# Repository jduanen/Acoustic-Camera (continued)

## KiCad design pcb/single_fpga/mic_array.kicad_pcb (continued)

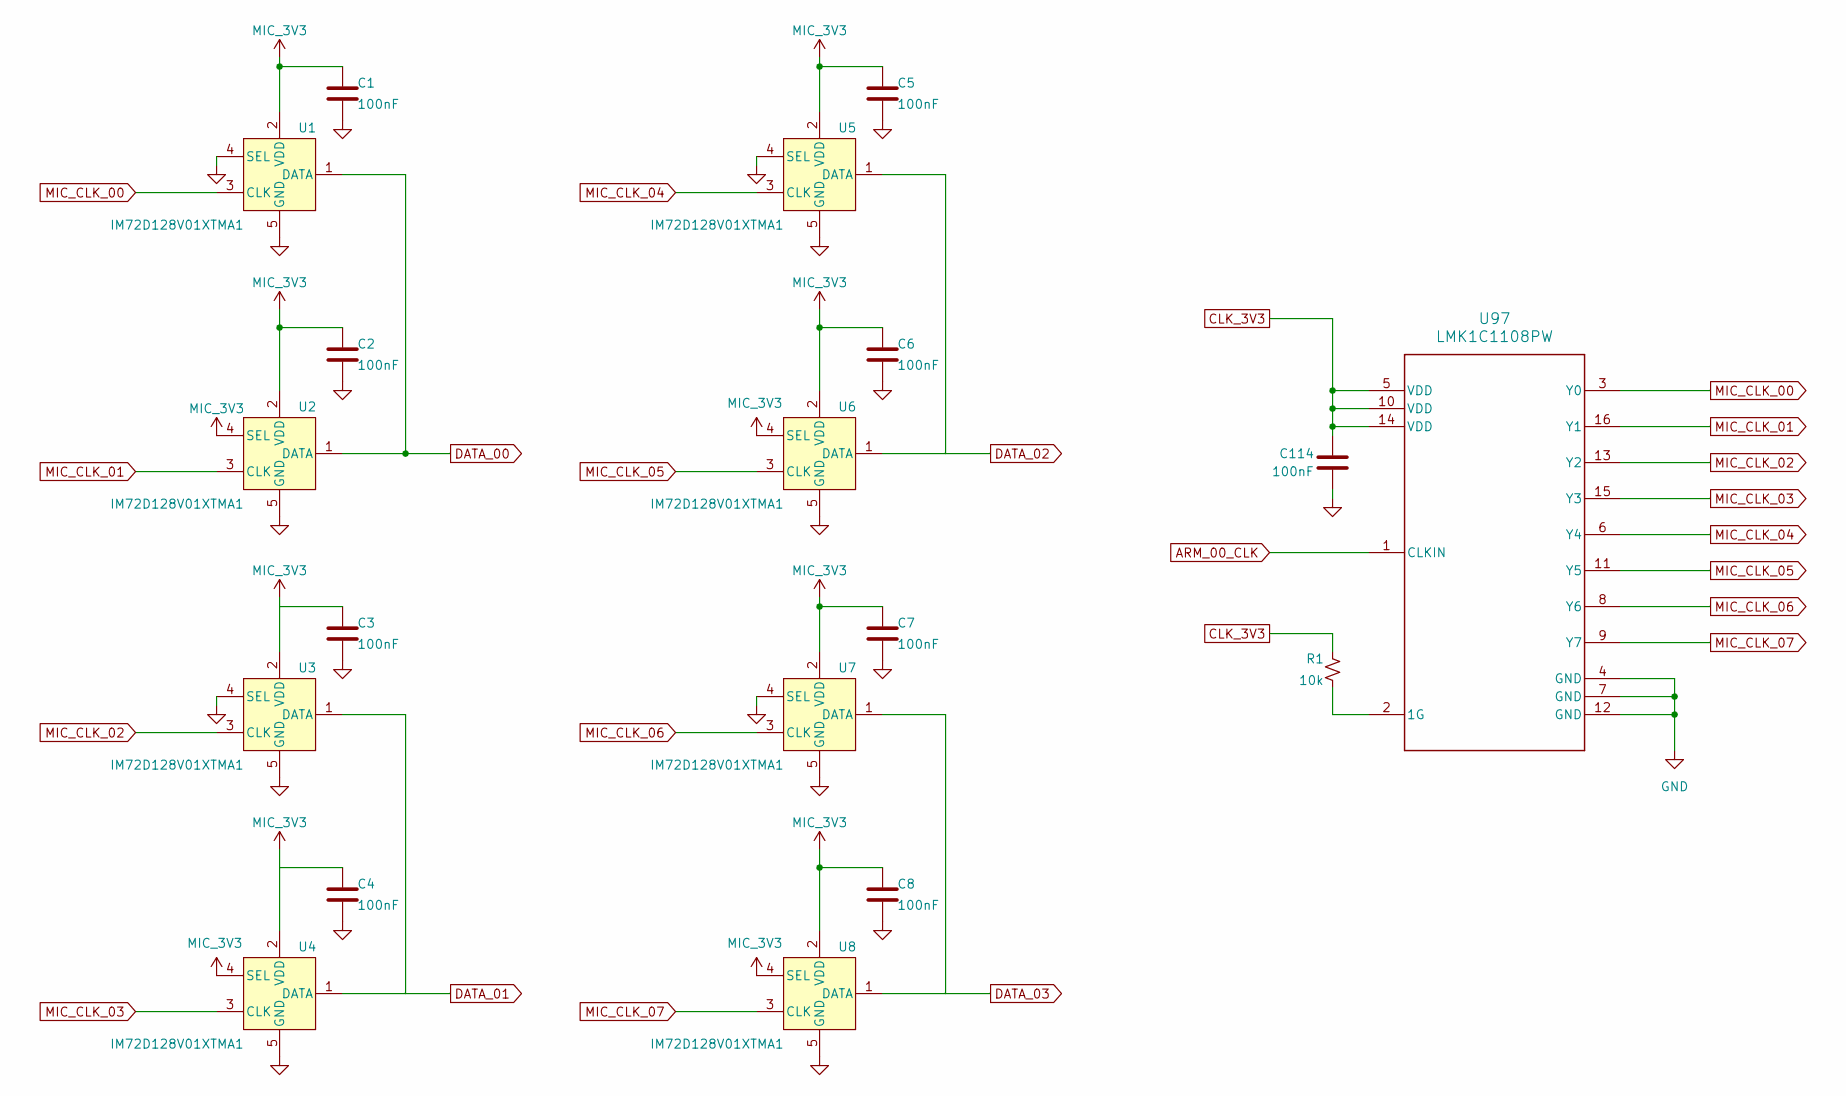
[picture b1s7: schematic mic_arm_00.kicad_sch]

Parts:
C1, C2, C3, C4, C5, C6, C7, C8, C114: 100nF; C_0603_1608Metric; Part Number CC0603KRX7R9BB104; LCSC Part # C14663
R1: 10k; R_0603_1608Metric; Part Number 0603WAF1002T5E; LCSC Part # C25804
U1, U2, U3, U4, U5, U6, U7, U8: IM72D128V01XTMA1; IFX-PG-LLGA-5-4; Part Number IM72D128V01XTMA1; LCSC Part # C5119248
U97: LMK1C1108PW; PW0016A_N; Part Number LMK1C1108PWR; LCSC Part # C2868241

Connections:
ARM_00_CLK: U97.1 (CLKIN); also elsewhere on the board
CLK_3V3: C114.2, R1.2, U97.5 (VDD), U97.10 (VDD), U97.14 (VDD); also elsewhere on the board
DATA_00: U1.1 (DATA), U2.1 (DATA); also elsewhere on the board
DATA_01: U3.1 (DATA), U4.1 (DATA); also elsewhere on the board
DATA_02: U5.1 (DATA), U6.1 (DATA); also elsewhere on the board
DATA_03: U7.1 (DATA), U8.1 (DATA); also elsewhere on the board
GND: C1.2, C2.2, C3.2, C4.2, C5.2, C6.2, C7.2, C8.2, C114.1, U1.4 (SEL), U1.5 (GND), U2.5 (GND), U3.4 (SEL), U3.5 (GND), U4.5 (GND), U5.4 (SEL), U5.5 (GND), U6.5 (GND), U7.4 (SEL), U7.5 (GND), U8.5 (GND), U97.4 (GND), U97.7 (GND), U97.12 (GND); also elsewhere on the board
MIC_3V3: C1.1, C2.1, C3.1, C4.1, C5.1, C6.1, C7.1, C8.1, U1.2 (VDD), U2.2 (VDD), U2.4 (SEL), U3.2 (VDD), U4.2 (VDD), U4.4 (SEL), U5.2 (VDD), U6.2 (VDD), U6.4 (SEL), U7.2 (VDD), U8.2 (VDD), U8.4 (SEL); also elsewhere on the board
MIC_CLK_00: U1.3 (CLK), U97.3 (Y0)
MIC_CLK_01: U2.3 (CLK), U97.16 (Y1)
MIC_CLK_02: U3.3 (CLK), U97.13 (Y2)
MIC_CLK_03: U4.3 (CLK), U97.15 (Y3)
MIC_CLK_04: U5.3 (CLK), U97.6 (Y4)
MIC_CLK_05: U6.3 (CLK), U97.11 (Y5)
MIC_CLK_06: U7.3 (CLK), U97.8 (Y6)
MIC_CLK_07: U8.3 (CLK), U97.9 (Y7)
unnamed: R1.1, U97.2 (1G)

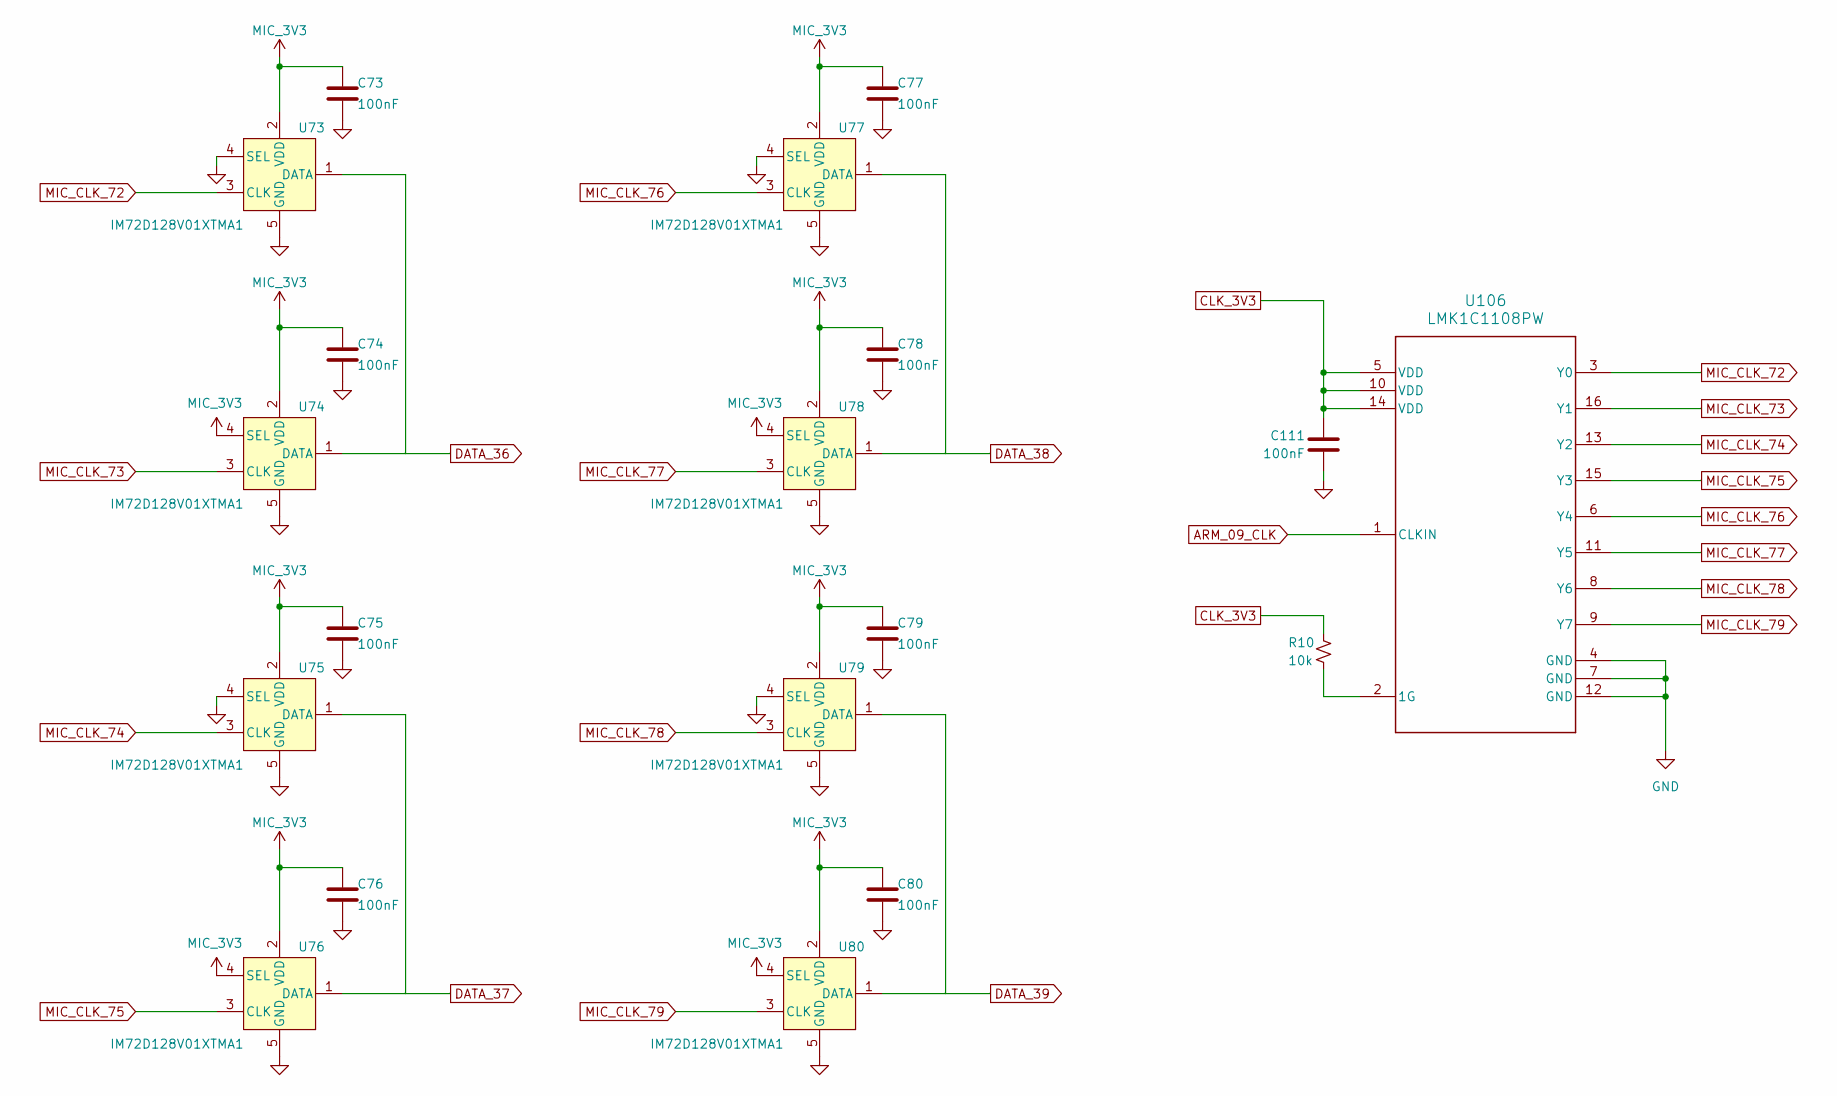
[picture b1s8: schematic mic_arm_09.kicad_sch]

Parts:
C73, C74, C75, C76, C77, C78, C79, C80, C111: 100nF; C_0603_1608Metric; Part Number CC0603KRX7R9BB104; LCSC Part # C14663
R10: 10k; R_0603_1608Metric; Part Number 0603WAF1002T5E; LCSC Part # C25804
U73, U74, U75, U76, U77, U78, U79, U80: IM72D128V01XTMA1; IFX-PG-LLGA-5-4; Part Number IM72D128V01XTMA1; LCSC Part # C5119248
U106: LMK1C1108PW; PW0016A_N; Part Number LMK1C1108PWR; LCSC Part # C2868241

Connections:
ARM_09_CLK: U106.1 (CLKIN); also elsewhere on the board
CLK_3V3: C111.2, R10.2, U106.5 (VDD), U106.10 (VDD), U106.14 (VDD); also elsewhere on the board
DATA_36: U73.1 (DATA), U74.1 (DATA); also elsewhere on the board
DATA_37: U75.1 (DATA), U76.1 (DATA); also elsewhere on the board
DATA_38: U77.1 (DATA), U78.1 (DATA); also elsewhere on the board
DATA_39: U79.1 (DATA), U80.1 (DATA); also elsewhere on the board
GND: C73.2, C74.2, C75.2, C76.2, C77.2, C78.2, C79.2, C80.2, C111.1, U73.4 (SEL), U73.5 (GND), U74.5 (GND), U75.4 (SEL), U75.5 (GND), U76.5 (GND), U77.4 (SEL), U77.5 (GND), U78.5 (GND), U79.4 (SEL), U79.5 (GND), U80.5 (GND), U106.4 (GND), U106.7 (GND), U106.12 (GND); also elsewhere on the board
MIC_3V3: C73.1, C74.1, C75.1, C76.1, C77.1, C78.1, C79.1, C80.1, U73.2 (VDD), U74.2 (VDD), U74.4 (SEL), U75.2 (VDD), U76.2 (VDD), U76.4 (SEL), U77.2 (VDD), U78.2 (VDD), U78.4 (SEL), U79.2 (VDD), U80.2 (VDD), U80.4 (SEL); also elsewhere on the board
MIC_CLK_72: U73.3 (CLK), U106.3 (Y0)
MIC_CLK_73: U74.3 (CLK), U106.16 (Y1)
MIC_CLK_74: U75.3 (CLK), U106.13 (Y2)
MIC_CLK_75: U76.3 (CLK), U106.15 (Y3)
MIC_CLK_76: U77.3 (CLK), U106.6 (Y4)
MIC_CLK_77: U78.3 (CLK), U106.11 (Y5)
MIC_CLK_78: U79.3 (CLK), U106.8 (Y6)
MIC_CLK_79: U80.3 (CLK), U106.9 (Y7)
unnamed: R10.1, U106.2 (1G)

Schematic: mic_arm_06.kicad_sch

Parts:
C49, C50, C51, C52, C53, C54, C55, C56, C108: 100nF; C_0603_1608Metric; Part Number CC0603KRX7R9BB104; LCSC Part # C14663
R7: 10k; R_0603_1608Metric; Part Number 0603WAF1002T5E; LCSC Part # C25804
U49, U50, U51, U52, U53, U54, U55, U56: IM72D128V01XTMA1; IFX-PG-LLGA-5-4; Part Number IM72D128V01XTMA1; LCSC Part # C5119248
U103: LMK1C1108PW; PW0016A_N; Part Number LMK1C1108PWR; LCSC Part # C2868241

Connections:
ARM_06_CLK: U103.1 (CLKIN); also elsewhere on the board
CLK_3V3: C108.2, R7.2, U103.5 (VDD), U103.10 (VDD), U103.14 (VDD); also elsewhere on the board
DATA_24: U49.1 (DATA), U50.1 (DATA); also elsewhere on the board
DATA_25: U51.1 (DATA), U52.1 (DATA); also elsewhere on the board
DATA_26: U53.1 (DATA), U54.1 (DATA); also elsewhere on the board
DATA_27: U55.1 (DATA), U56.1 (DATA); also elsewhere on the board
GND: C49.2, C50.2, C51.2, C52.2, C53.2, C54.2, C55.2, C56.2, C108.1, U49.4 (SEL), U49.5 (GND), U50.5 (GND), U51.4 (SEL), U51.5 (GND), U52.5 (GND), U53.4 (SEL), U53.5 (GND), U54.5 (GND), U55.4 (SEL), U55.5 (GND), U56.5 (GND), U103.4 (GND), U103.7 (GND), U103.12 (GND); also elsewhere on the board
MIC_3V3: C49.1, C50.1, C51.1, C52.1, C53.1, C54.1, C55.1, C56.1, U49.2 (VDD), U50.2 (VDD), U50.4 (SEL), U51.2 (VDD), U52.2 (VDD), U52.4 (SEL), U53.2 (VDD), U54.2 (VDD), U54.4 (SEL), U55.2 (VDD), U56.2 (VDD), U56.4 (SEL); also elsewhere on the board
MIC_CLK_48: U49.3 (CLK), U103.3 (Y0)
MIC_CLK_49: U50.3 (CLK), U103.16 (Y1)
MIC_CLK_50: U51.3 (CLK), U103.13 (Y2)
MIC_CLK_51: U52.3 (CLK), U103.15 (Y3)
MIC_CLK_52: U53.3 (CLK), U103.6 (Y4)
MIC_CLK_53: U54.3 (CLK), U103.11 (Y5)
MIC_CLK_54: U55.3 (CLK), U103.8 (Y6)
MIC_CLK_55: U56.3 (CLK), U103.9 (Y7)
unnamed: R7.1, U103.2 (1G)

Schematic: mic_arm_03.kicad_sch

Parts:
C25, C26, C27, C28, C29, C30, C31, C32, C105: 100nF; C_0603_1608Metric; Part Number CC0603KRX7R9BB104; LCSC Part # C14663
R4: 10k; R_0603_1608Metric; Part Number 0603WAF1002T5E; LCSC Part # C25804
U25, U26, U27, U28, U29, U30, U31, U32: IM72D128V01XTMA1; IFX-PG-LLGA-5-4; Part Number IM72D128V01XTMA1; LCSC Part # C5119248
U100: LMK1C1108PW; PW0016A_N; Part Number LMK1C1108PWR; LCSC Part # C2868241

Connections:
ARM_03_CLK: U100.1 (CLKIN); also elsewhere on the board
CLK_3V3: C105.2, R4.2, U100.5 (VDD), U100.10 (VDD), U100.14 (VDD); also elsewhere on the board
DATA_12: U25.1 (DATA), U26.1 (DATA); also elsewhere on the board
DATA_13: U27.1 (DATA), U28.1 (DATA); also elsewhere on the board
DATA_14: U29.1 (DATA), U30.1 (DATA); also elsewhere on the board
DATA_15: U31.1 (DATA), U32.1 (DATA); also elsewhere on the board
GND: C25.2, C26.2, C27.2, C28.2, C29.2, C30.2, C31.2, C32.2, C105.1, U25.4 (SEL), U25.5 (GND), U26.5 (GND), U27.4 (SEL), U27.5 (GND), U28.5 (GND), U29.4 (SEL), U29.5 (GND), U30.5 (GND), U31.4 (SEL), U31.5 (GND), U32.5 (GND), U100.4 (GND), U100.7 (GND), U100.12 (GND); also elsewhere on the board
MIC_3V3: C25.1, C26.1, C27.1, C28.1, C29.1, C30.1, C31.1, C32.1, U25.2 (VDD), U26.2 (VDD), U26.4 (SEL), U27.2 (VDD), U28.2 (VDD), U28.4 (SEL), U29.2 (VDD), U30.2 (VDD), U30.4 (SEL), U31.2 (VDD), U32.2 (VDD), U32.4 (SEL); also elsewhere on the board
MIC_CLK_24: U25.3 (CLK), U100.3 (Y0)
MIC_CLK_25: U26.3 (CLK), U100.16 (Y1)
MIC_CLK_26: U27.3 (CLK), U100.13 (Y2)
MIC_CLK_27: U28.3 (CLK), U100.15 (Y3)
MIC_CLK_28: U29.3 (CLK), U100.6 (Y4)
MIC_CLK_29: U30.3 (CLK), U100.11 (Y5)
MIC_CLK_30: U31.3 (CLK), U100.8 (Y6)
MIC_CLK_31: U32.3 (CLK), U100.9 (Y7)
unnamed: R4.1, U100.2 (1G)

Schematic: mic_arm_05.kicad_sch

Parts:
C41, C42, C43, C44, C45, C46, C47, C48, C107: 100nF; C_0603_1608Metric; Part Number CC0603KRX7R9BB104; LCSC Part # C14663
R6: 10k; R_0603_1608Metric; Part Number 0603WAF1002T5E; LCSC Part # C25804
U41, U42, U43, U44, U45, U46, U47, U48: IM72D128V01XTMA1; IFX-PG-LLGA-5-4; Part Number IM72D128V01XTMA1; LCSC Part # C5119248
U102: LMK1C1108PW; PW0016A_N; Part Number LMK1C1108PWR; LCSC Part # C2868241

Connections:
ARM_05_CLK: U102.1 (CLKIN); also elsewhere on the board
CLK_3V3: C107.2, R6.2, U102.5 (VDD), U102.10 (VDD), U102.14 (VDD); also elsewhere on the board
DATA_20: U41.1 (DATA), U42.1 (DATA); also elsewhere on the board
DATA_21: U43.1 (DATA), U44.1 (DATA); also elsewhere on the board
DATA_22: U45.1 (DATA), U46.1 (DATA); also elsewhere on the board
DATA_23: U47.1 (DATA), U48.1 (DATA); also elsewhere on the board
GND: C41.2, C42.2, C43.2, C44.2, C45.2, C46.2, C47.2, C48.2, C107.1, U41.4 (SEL), U41.5 (GND), U42.5 (GND), U43.4 (SEL), U43.5 (GND), U44.5 (GND), U45.4 (SEL), U45.5 (GND), U46.5 (GND), U47.4 (SEL), U47.5 (GND), U48.5 (GND), U102.4 (GND), U102.7 (GND), U102.12 (GND); also elsewhere on the board
MIC_3V3: C41.1, C42.1, C43.1, C44.1, C45.1, C46.1, C47.1, C48.1, U41.2 (VDD), U42.2 (VDD), U42.4 (SEL), U43.2 (VDD), U44.2 (VDD), U44.4 (SEL), U45.2 (VDD), U46.2 (VDD), U46.4 (SEL), U47.2 (VDD), U48.2 (VDD), U48.4 (SEL); also elsewhere on the board
MIC_CLK_40: U41.3 (CLK), U102.3 (Y0)
MIC_CLK_41: U42.3 (CLK), U102.16 (Y1)
MIC_CLK_42: U43.3 (CLK), U102.13 (Y2)
MIC_CLK_43: U44.3 (CLK), U102.15 (Y3)
MIC_CLK_44: U45.3 (CLK), U102.6 (Y4)
MIC_CLK_45: U46.3 (CLK), U102.11 (Y5)
MIC_CLK_46: U47.3 (CLK), U102.8 (Y6)
MIC_CLK_47: U48.3 (CLK), U102.9 (Y7)
unnamed: R6.1, U102.2 (1G)

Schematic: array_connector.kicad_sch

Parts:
J1: AXK6S80637YG; Part Number AXK6S80637YG; LCSC Part # C2936859

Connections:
+3V6: J1.1, J1.2, J1.3, J1.4, J1.5, J1.6, J1.7, J1.8; also elsewhere on the board
DATA_00: J1.11; also elsewhere on the board
DATA_01: J1.12; also elsewhere on the board
DATA_02: J1.13; also elsewhere on the board
DATA_03: J1.14; also elsewhere on the board
DATA_04: J1.15; also elsewhere on the board
DATA_05: J1.16; also elsewhere on the board
DATA_06: J1.17; also elsewhere on the board
DATA_07: J1.18; also elsewhere on the board
DATA_08: J1.21; also elsewhere on the board
DATA_09: J1.22; also elsewhere on the board
DATA_10: J1.23; also elsewhere on the board
DATA_11: J1.24; also elsewhere on the board
DATA_12: J1.25; also elsewhere on the board
DATA_13: J1.26; also elsewhere on the board
DATA_14: J1.27; also elsewhere on the board
DATA_15: J1.28; also elsewhere on the board
DATA_16: J1.31; also elsewhere on the board
DATA_17: J1.32; also elsewhere on the board
DATA_18: J1.33; also elsewhere on the board
DATA_19: J1.34; also elsewhere on the board
DATA_20: J1.35; also elsewhere on the board
DATA_21: J1.36; also elsewhere on the board
DATA_22: J1.37; also elsewhere on the board
DATA_23: J1.38; also elsewhere on the board
DATA_24: J1.78; also elsewhere on the board
DATA_25: J1.77; also elsewhere on the board
DATA_26: J1.76; also elsewhere on the board
DATA_27: J1.75; also elsewhere on the board
DATA_28: J1.74; also elsewhere on the board
DATA_29: J1.73; also elsewhere on the board
DATA_30: J1.72; also elsewhere on the board
DATA_31: J1.71; also elsewhere on the board
DATA_32: J1.68; also elsewhere on the board
DATA_33: J1.67; also elsewhere on the board
DATA_34: J1.66; also elsewhere on the board
DATA_35: J1.65; also elsewhere on the board
DATA_36: J1.64; also elsewhere on the board
DATA_37: J1.63; also elsewhere on the board
DATA_38: J1.62; also elsewhere on the board
DATA_39: J1.61; also elsewhere on the board
DATA_40: J1.58; also elsewhere on the board
DATA_41: J1.57; also elsewhere on the board
DATA_42: J1.56; also elsewhere on the board
DATA_43: J1.55; also elsewhere on the board
DATA_44: J1.54; also elsewhere on the board
DATA_45: J1.53; also elsewhere on the board
DATA_46: J1.52; also elsewhere on the board
DATA_47: J1.51; also elsewhere on the board
GND: J1.9, J1.10, J1.19, J1.20, J1.29, J1.30, J1.39, J1.40, J1.43, J1.49, J1.50, J1.59, J1.60, J1.69, J1.70, J1.79, J1.80; also elsewhere on the board
PDM_CLK: J1.45; also elsewhere on the board
TCXO_CLK: J1.41; also elsewhere on the board

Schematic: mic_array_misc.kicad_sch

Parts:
C117, C118, C119, C120, C121, C122, C123, C124, C125, C126, C127, C128, C129, C130, C131, C132, C133, C134, C135, C136, C137, C138, C139, C140, C141, C142, C143, C144, C145, C146, C147, C148, C149, C150, C151, C152, C153, C154, C155, C156, C157, C158, C159, C160, C161, C162, C163, C164, C165, C166, C167, C168, C169, C170, C171, C172, C173, C174, C175, C176, C177, C178, C179, C180, C181, C182, C183: 100nF; C_0603_1608Metric; Part Number CC0603KRX7R9BB104; LCSC Part # C14663
C184, C185: 100nF; C_0402_1005Metric; Part Number CL05B104KO5NNNC; LCSC Part # C1525
TP1: GND; TestPoint_THTPad_D2.0mm_Drill1.0mm
TP2: MIC 3V3; TestPoint_THTPad_D2.0mm_Drill1.0mm
TP3: 3V6; TestPoint_THTPad_D2.0mm_Drill1.0mm
TP4: CLK 3V3; TestPoint_THTPad_D2.0mm_Drill1.0mm

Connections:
+3V6: TP3.1 (1_1); also elsewhere on the board
CLK_3V3: C138.1, C139.1, C140.1, C141.1, C142.1, C143.1, C144.1, C145.1, C146.1, C147.1, C148.1, C149.1, C150.1, C151.1, C152.1, C153.1, C154.1, C155.1, C156.1, C184.1, C185.1, TP4.1 (1_1); also elsewhere on the board
GND: C117.2, C118.2, C119.2, C120.2, C121.2, C122.2, C123.2, C124.2, C125.2, C126.2, C127.2, C128.2, C129.2, C130.2, C131.2, C132.2, C133.2, C134.2, C135.2, C136.2, C137.2, C138.2, C139.2, C140.2, C141.2, C142.2, C143.2, C144.2, C145.2, C146.2, C147.2, C148.2, C149.2, C150.2, C151.2, C152.2, C153.2, C154.2, C155.2, C156.2, C157.2, C158.2, C159.2, C160.2, C161.2, C162.2, C163.2, C164.2, C165.2, C166.2, C167.2, C168.2, C169.2, C170.2, C171.2, C172.2, C173.2, C174.2, C175.2, C176.2, C177.2, C178.2, C179.2, C180.2, C181.2, C182.2, C183.2, C184.2, C185.2, TP1.1 (1_1); also elsewhere on the board
MIC_3V3: C117.1, C118.1, C119.1, C120.1, C121.1, C122.1, C123.1, C124.1, C125.1, C126.1, C127.1, C128.1, C129.1, C130.1, C131.1, C132.1, C133.1, C134.1, C135.1, C136.1, C137.1, C157.1, C158.1, C159.1, C160.1, C161.1, C162.1, C163.1, C164.1, C165.1, C166.1, C167.1, C168.1, C169.1, C170.1, C171.1, C172.1, C173.1, C174.1, C175.1, C176.1, C177.1, C178.1, C179.1, C180.1, C181.1, C182.1, C183.1, TP2.1 (1_1); also elsewhere on the board

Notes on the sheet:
Clock return-path stitching caps C117–C137 (GND–MIC_3V3), each next to a clock F.Cu/B.Cu via with no GND via or GND–MIC_3V3 cap within 10 mm. See SCHEMATIC_NOTES.md.
C184/C185: extra CLK_3V3 decoupling for U103/U105 (no room right at their VDD pins; placed on each buffer's CLK_3V3 feed).
Clock-buffer VDD decoupling C138–C156 (100 nF): on F.Cu next to U110 and the arm CDCLVC1108s, tied into each buffer's CLK_3V3 trace. See SCHEMATIC_NOTES.md.
Test Points -- through holes for 0.025" posts
Clock/J1 return-path stitching caps C157–C183 (GND–MIC_3V3), next to F.Cu/B.Cu signal vias that had no GND–MIC_3V3 cap within 10 mm (clocks) or 5 mm (around J1). See SCHEMATIC_NOTES.md.

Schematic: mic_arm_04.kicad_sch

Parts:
C33, C34, C35, C36, C37, C38, C39, C40, C106: 100nF; C_0603_1608Metric; Part Number CC0603KRX7R9BB104; LCSC Part # C14663
R5: 10k; R_0603_1608Metric; Part Number 0603WAF1002T5E; LCSC Part # C25804
U33, U34, U35, U36, U37, U38, U39, U40: IM72D128V01XTMA1; IFX-PG-LLGA-5-4; Part Number IM72D128V01XTMA1; LCSC Part # C5119248
U101: LMK1C1108PW; PW0016A_N; Part Number LMK1C1108PWR; LCSC Part # C2868241

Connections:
ARM_04_CLK: U101.1 (CLKIN); also elsewhere on the board
CLK_3V3: C106.1, R5.2, U101.5 (VDD), U101.10 (VDD), U101.14 (VDD); also elsewhere on the board
DATA_16: U33.1 (DATA), U34.1 (DATA); also elsewhere on the board
DATA_17: U35.1 (DATA), U36.1 (DATA); also elsewhere on the board
DATA_18: U37.1 (DATA), U38.1 (DATA); also elsewhere on the board
DATA_19: U39.1 (DATA), U40.1 (DATA); also elsewhere on the board
GND: C33.2, C34.2, C35.2, C36.2, C37.2, C38.2, C39.2, C40.2, C106.2, U33.4 (SEL), U33.5 (GND), U34.5 (GND), U35.4 (SEL), U35.5 (GND), U36.5 (GND), U37.4 (SEL), U37.5 (GND), U38.5 (GND), U39.4 (SEL), U39.5 (GND), U40.5 (GND), U101.4 (GND), U101.7 (GND), U101.12 (GND); also elsewhere on the board
MIC_3V3: C33.1, C34.1, C35.1, C36.1, C37.1, C38.1, C39.1, C40.1, U33.2 (VDD), U34.2 (VDD), U34.4 (SEL), U35.2 (VDD), U36.2 (VDD), U36.4 (SEL), U37.2 (VDD), U38.2 (VDD), U38.4 (SEL), U39.2 (VDD), U40.2 (VDD), U40.4 (SEL); also elsewhere on the board
MIC_CLK_32: U33.3 (CLK), U101.3 (Y0)
MIC_CLK_33: U34.3 (CLK), U101.16 (Y1)
MIC_CLK_34: U35.3 (CLK), U101.13 (Y2)
MIC_CLK_35: U36.3 (CLK), U101.15 (Y3)
MIC_CLK_36: U37.3 (CLK), U101.6 (Y4)
MIC_CLK_37: U38.3 (CLK), U101.11 (Y5)
MIC_CLK_38: U39.3 (CLK), U101.8 (Y6)
MIC_CLK_39: U40.3 (CLK), U101.9 (Y7)
unnamed: R5.1, U101.2 (1G)

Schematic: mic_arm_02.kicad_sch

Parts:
C17, C18, C19, C20, C21, C22, C23, C24, C116: 100nF; C_0603_1608Metric; Part Number CC0603KRX7R9BB104; LCSC Part # C14663
R3: 10k; R_0603_1608Metric; Part Number 0603WAF1002T5E; LCSC Part # C25804
U17, U18, U19, U20, U21, U22, U23, U24: IM72D128V01XTMA1; IFX-PG-LLGA-5-4; Part Number IM72D128V01XTMA1; LCSC Part # C5119248
U99: LMK1C1108PW; PW0016A_N; Part Number LMK1C1108PWR; LCSC Part # C2868241

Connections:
ARM_02_CLK: U99.1 (CLKIN); also elsewhere on the board
CLK_3V3: C116.2, R3.2, U99.5 (VDD), U99.10 (VDD), U99.14 (VDD); also elsewhere on the board
DATA_08: U17.1 (DATA), U18.1 (DATA); also elsewhere on the board
DATA_09: U19.1 (DATA), U20.1 (DATA); also elsewhere on the board
DATA_10: U21.1 (DATA), U22.1 (DATA); also elsewhere on the board
DATA_11: U23.1 (DATA), U24.1 (DATA); also elsewhere on the board
GND: C17.2, C18.2, C19.2, C20.2, C21.2, C22.2, C23.2, C24.2, C116.1, U17.4 (SEL), U17.5 (GND), U18.5 (GND), U19.4 (SEL), U19.5 (GND), U20.5 (GND), U21.4 (SEL), U21.5 (GND), U22.5 (GND), U23.4 (SEL), U23.5 (GND), U24.5 (GND), U99.4 (GND), U99.7 (GND), U99.12 (GND); also elsewhere on the board
MIC_3V3: C17.1, C18.1, C19.1, C20.1, C21.1, C22.1, C23.1, C24.1, U17.2 (VDD), U18.2 (VDD), U18.4 (SEL), U19.2 (VDD), U20.2 (VDD), U20.4 (SEL), U21.2 (VDD), U22.2 (VDD), U22.4 (SEL), U23.2 (VDD), U24.2 (VDD), U24.4 (SEL); also elsewhere on the board
MIC_CLK_16: U17.3 (CLK), U99.3 (Y0)
MIC_CLK_17: U18.3 (CLK), U99.16 (Y1)
MIC_CLK_18: U19.3 (CLK), U99.13 (Y2)
MIC_CLK_19: U20.3 (CLK), U99.15 (Y3)
MIC_CLK_20: U21.3 (CLK), U99.6 (Y4)
MIC_CLK_21: U22.3 (CLK), U99.11 (Y5)
MIC_CLK_22: U23.3 (CLK), U99.8 (Y6)
MIC_CLK_23: U24.3 (CLK), U99.9 (Y7)
unnamed: R3.1, U99.2 (1G)

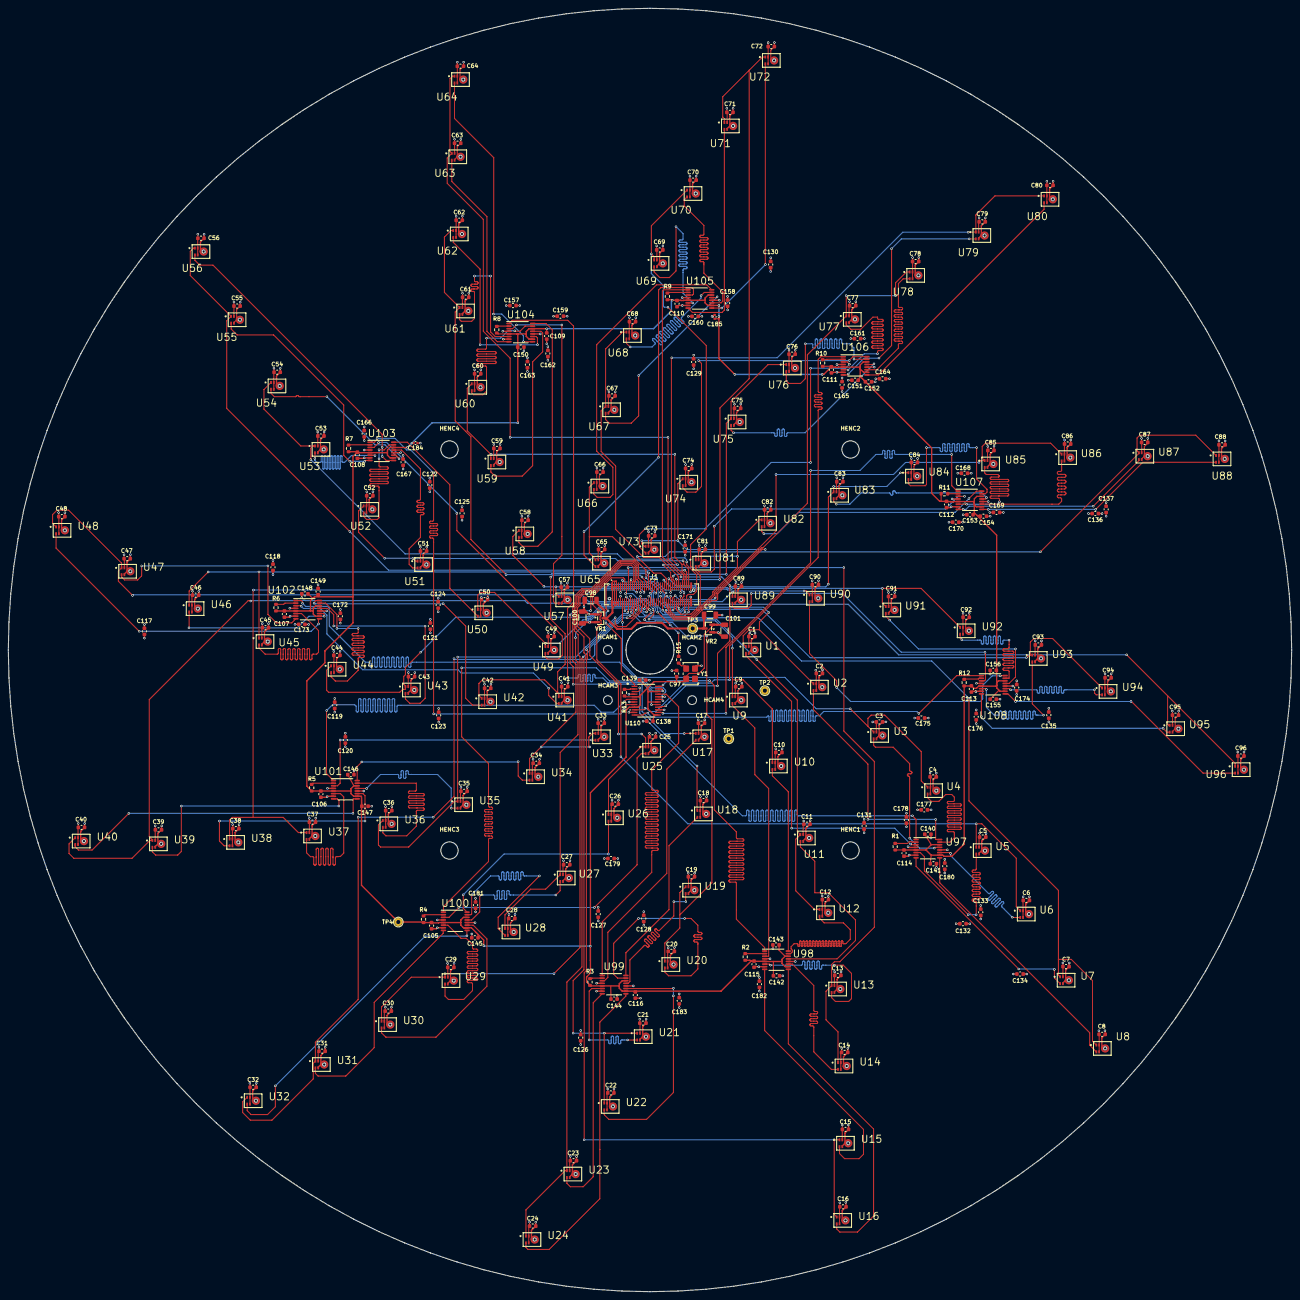
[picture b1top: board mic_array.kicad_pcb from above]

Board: 4 copper layers, 320.0 x 320.0 mm, 321 parts (0 on the bottom side), 176 nets.

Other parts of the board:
HCAM1, HCAM2, HCAM3, HCAM4: MountingHole_2.2mm_M2
HENC1, HENC2, HENC3, HENC4: MountingHole_4.3mm_M4

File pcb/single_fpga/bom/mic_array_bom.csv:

"Refs","Qty","Value","Footprint","Manufacturer","Part Number","LCSC Part #","PROD_ID","Tolerance","Voltage","Description"
"C1,C2,C3,C4,C5,C6,C7,C8,C9,C10,C11,C12,C13,C14,C15,C16,C17,C18,C19,C20,C21,C22,C23,C24,C25,C26,C27,C28,C29,C30,C31,C32,C33,C34,C35,C36,C37,C38,C39,C40,C41,C42,C43,C44,C45,C46,C47,C48,C49,C50,C51,C52,C53,C54,C55,C56,C57,C58,C59,C60,C61,C62,C63,C64,C65,C66,C67,C68,C69,C70,C71,C72,C73,C74,C75,C76,C77,C78,C79,C80,C81,C82,C83,C84,C85,C86,C87,C88,C89,C90,C91,C92,C93,C94,C95,C96,C97,C105,C106,C107,C108,C109,C110,C111,C112,C113,C114,C115,C116,C117,C118,C119,C120,C121,C122,C123,C124,C125,C126,C127,C128,C129,C130,C131,C132,C133,C134,C135,C136,C137,C138,C139,C140,C141,C142,C143,C144,C145,C146,C147,C148,C149,C150,C151,C152,C153,C154,C155,C156,C157,C158,C159,C160,C161,C162,C163,C164,C165,C166,C167,C168,C169,C170,C171,C172,C173,C174,C175,C176,C177,C178,C179,C180,C181,C182,C183","176","100nF","Capacitor_SMD:C_0603_1608Metric","YAGEO","CC0603KRX7R9BB104","C14663","","","","Unpolarized capacitor"
"C98,C99,C100,C101","4","1uF","Capacitor_SMD:C_1206_3216Metric","Samsung Electro-Mechanics","CL31B105KBHNNNE","C1848","","","","Unpolarized capacitor"
"C184,C185","2","100nF","Capacitor_SMD:C_0402_1005Metric","Samsung Electro-Mechanics","CL05B104KO5NNNC","C1525","","","","Unpolarized capacitor"
"J1","1","AXK6S80637YG","AXK6S80637YG:AXK6S80637YG","Panasonic","AXK6S80637YG","C2936859","","","","Panasonic AXK6S80637YG -- P5KS 0.5mm-pitch 80-pin board-to-board HEADER, 6.0/6.5/9.0mm mated height, with positioning bosses. Mates AXK5S80337YG at 9.0mm."
"R1,R2,R3,R4,R5,R6,R7,R8,R9,R10,R11,R12,R13","13","10k","PCM_SparkFun-Resistor:R_0603_1608Metric","UNI-ROYAL","0603WAF1002T5E","C25804","RES-00824","","","Resistor"
"R15","1","33","PCM_SparkFun-Resistor:R_0603_1608Metric","UNI-ROYAL","0603WAF330JT5E","C23140","","","","Resistor"
"U1,U2,U3,U4,U5,U6,U7,U8,U9,U10,U11,U12,U13,U14,U15,U16,U17,U18,U19,U20,U21,U22,U23,U24,U25,U26,U27,U28,U29,U30,U31,U32,U33,U34,U35,U36,U37,U38,U39,U40,U41,U42,U43,U44,U45,U46,U47,U48,U49,U50,U51,U52,U53,U54,U55,U56,U57,U58,U59,U60,U61,U62,U63,U64,U65,U66,U67,U68,U69,U70,U71,U72,U73,U74,U75,U76,U77,U78,U79,U80,U81,U82,U83,U84,U85,U86,U87,U88,U89,U90,U91,U92,U93,U94,U95,U96","96","IM72D128V01XTMA1","IM72D128:IFX-PG-LLGA-5-4","Infineon","IM72D128V01XTMA1","C5119248","","","","Infineon IM72D128 PDM MEMS mic, 72 dB SNR, IP57"
"U97,U98,U99,U100,U101,U102,U103,U104,U105,U106,U107,U108","12","LMK1C1108PW","CDCLVC1108:PW0016A_N","Texas Instruments","LMK1C1108PWR","C2868241","","","",""
"U110","1","CDCLVC1112PW","CDCLVC1112:PW24","Texas Instruments","CDCLVC1112PWR","C2876940","","","",""
"VR1,VR2","2","MCP1700T-3302E/TT","Package_TO_SOT_SMD:SOT-23","Microchip","MCP1700T-3302E/TT","C39051","","","","250mA Low Quiscent Current LDO, 3.3V output, SOT-23"
"Y1","1","ASFL1-12.288MHZ","Oscillator:Oscillator_SMD_SeikoEpson_SG8002LB-4Pin_5.0x3.2mm","Abracon","ASFL1-12.288MHZ-LCS-T","C276419","","","","Master clock: Abracon ASFL1-12.288MHZ-LCS-T, 12.288 MHz 3.3 V HCMOS oscillator, ±50 ppm, -40 to +85 °C, 5.0x3.2 mm. Pin 1 is tri-state (open = running) and is left unconnected."

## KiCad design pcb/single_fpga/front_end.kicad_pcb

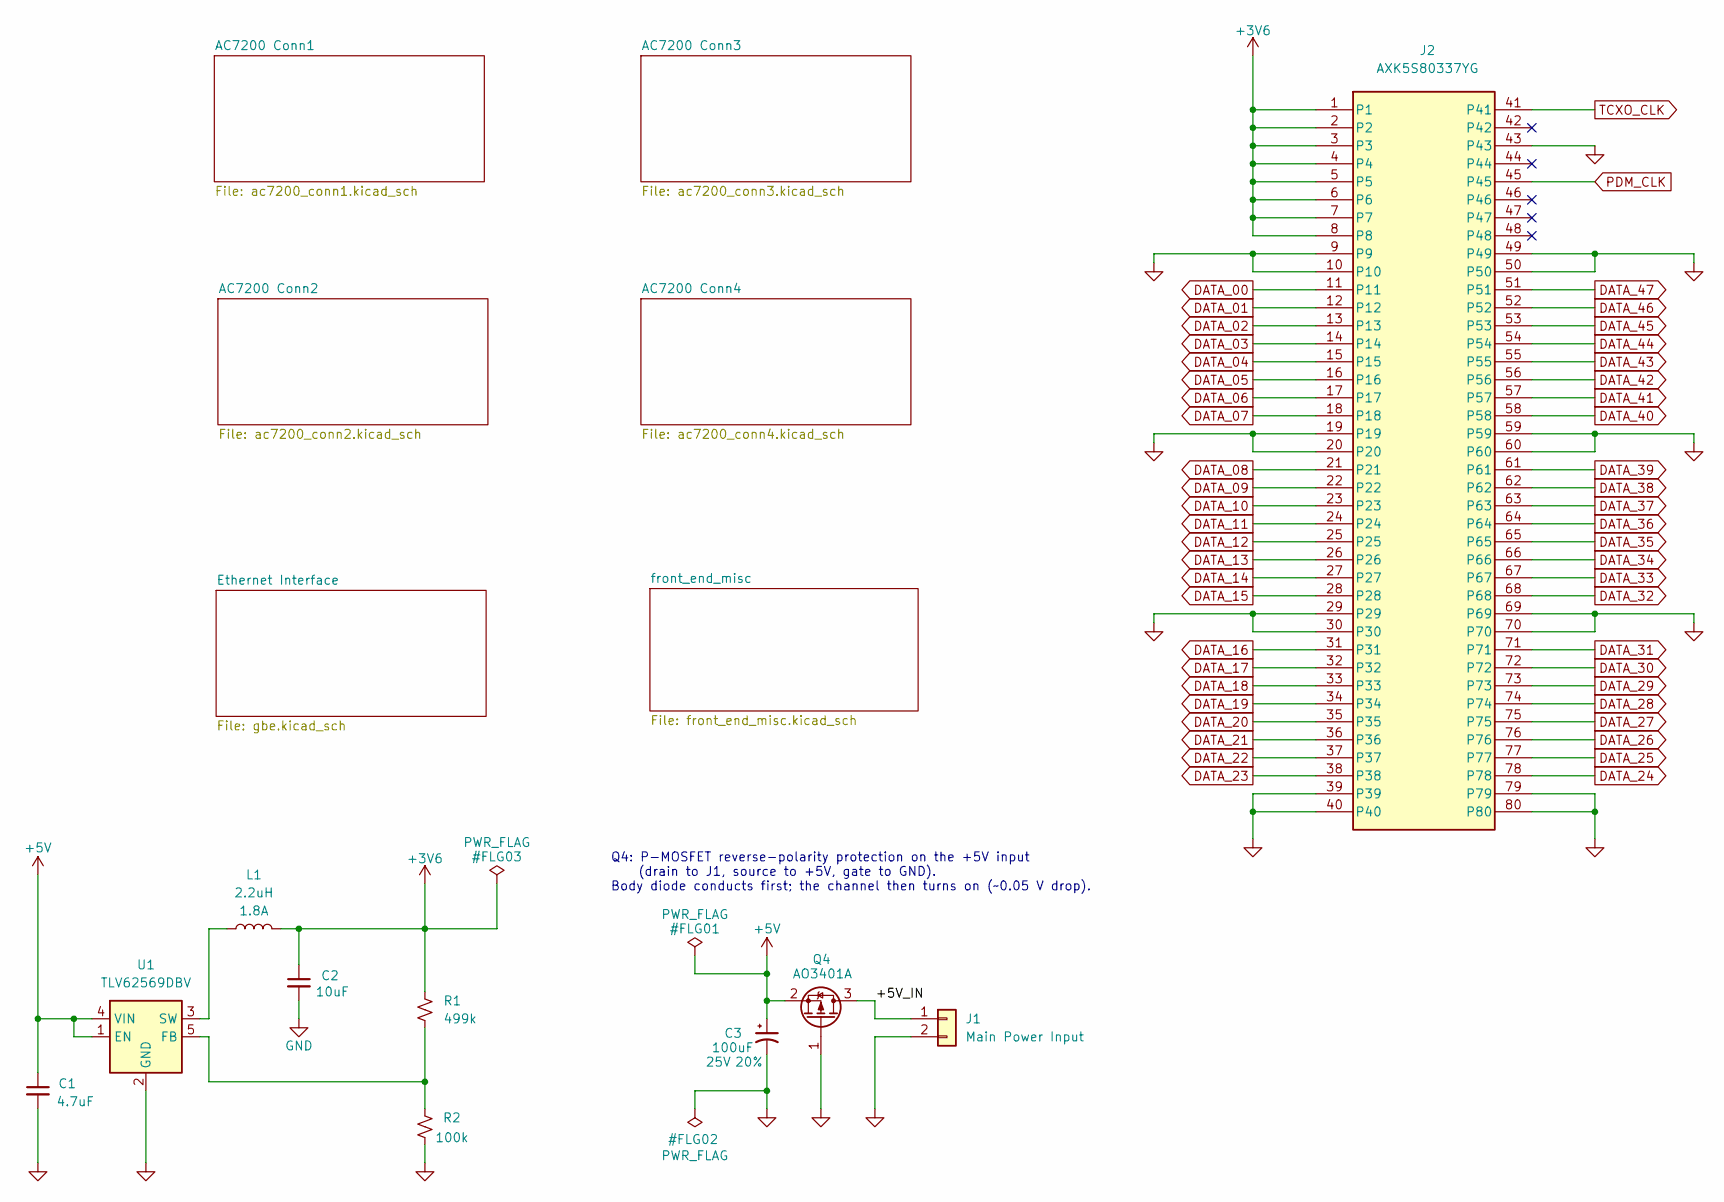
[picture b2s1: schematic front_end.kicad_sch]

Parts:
C1: 4.7uF; C_0805_2012Metric; Voltage 16V; Tolerance 10%; Part Number CL21B475KOFNNNE; LCSC Part # C107365
C2: 10uF; C_0805_2012Metric; Voltage 10V; Tolerance 10%; Part Number GRM21BR71A106KE51L; LCSC Part # C86038
C3: 100uF; CP_Elec_6.3x5.8; Voltage 25V; Tolerance 20%; Part Number FVM025ADA101M0654; LCSC Part # C7469933
J1: Main Power Input; JST_XH_B2B-XH-A_1x02_P2.50mm_Vertical; Part Number B2B-XH-A(LF)(SN); LCSC Part # C158012
J2: AXK5S80337YG; Part Number AXK5S80337YG
L1: 2.2uH; L_Murata_DFE201610P; Part Number DFE201612E-2R2M=P2; LCSC Part # C337893
Q4: AO3401A; SOT-23; Part Number AO3401A; LCSC Part # C15127
R1: 499k; R_0603_1608Metric; Tolerance 1%; Part Number RC0603FR-07499KL; LCSC Part # C131054
R2: 100k; R_0603_1608Metric; Tolerance 1%; Part Number 0603WAF1003T5E; LCSC Part # C25803
U1: TLV62569DBV; SOT-23-5; Part Number TLV62569DBVR; LCSC Part # C141836

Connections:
+3V6: C2.1, J2.1, J2.2, J2.3, J2.4, J2.5, J2.6, J2.7, J2.8, L1.2, R1.1; also elsewhere on the board
+5V: C1.1, C3.1, Q4.2 (S), U1.1 (EN), U1.4 (VIN); also elsewhere on the board
/+5V_IN: J1.1, Q4.3 (D)
DATA_00: J2.11; also elsewhere on the board
DATA_01: J2.12; also elsewhere on the board
DATA_02: J2.13; also elsewhere on the board
DATA_03: J2.14; also elsewhere on the board
DATA_04: J2.15; also elsewhere on the board
DATA_05: J2.16; also elsewhere on the board
DATA_06: J2.17; also elsewhere on the board
DATA_07: J2.18; also elsewhere on the board
DATA_08: J2.21; also elsewhere on the board
DATA_09: J2.22; also elsewhere on the board
DATA_10: J2.23; also elsewhere on the board
DATA_11: J2.24; also elsewhere on the board
DATA_12: J2.25; also elsewhere on the board
DATA_13: J2.26; also elsewhere on the board
DATA_14: J2.27; also elsewhere on the board
DATA_15: J2.28; also elsewhere on the board
DATA_16: J2.31; also elsewhere on the board
DATA_17: J2.32; also elsewhere on the board
DATA_18: J2.33; also elsewhere on the board
DATA_19: J2.34; also elsewhere on the board
DATA_20: J2.35; also elsewhere on the board
DATA_21: J2.36; also elsewhere on the board
DATA_22: J2.37; also elsewhere on the board
DATA_23: J2.38; also elsewhere on the board
DATA_24: J2.78; also elsewhere on the board
DATA_25: J2.77; also elsewhere on the board
DATA_26: J2.76; also elsewhere on the board
DATA_27: J2.75; also elsewhere on the board
DATA_28: J2.74; also elsewhere on the board
DATA_29: J2.73; also elsewhere on the board
DATA_30: J2.72; also elsewhere on the board
DATA_31: J2.71; also elsewhere on the board
DATA_32: J2.68; also elsewhere on the board
DATA_33: J2.67; also elsewhere on the board
DATA_34: J2.66; also elsewhere on the board
DATA_35: J2.65; also elsewhere on the board
DATA_36: J2.64; also elsewhere on the board
DATA_37: J2.63; also elsewhere on the board
DATA_38: J2.62; also elsewhere on the board
DATA_39: J2.61; also elsewhere on the board
DATA_40: J2.58; also elsewhere on the board
DATA_41: J2.57; also elsewhere on the board
DATA_42: J2.56; also elsewhere on the board
DATA_43: J2.55; also elsewhere on the board
DATA_44: J2.54; also elsewhere on the board
DATA_45: J2.53; also elsewhere on the board
DATA_46: J2.52; also elsewhere on the board
DATA_47: J2.51; also elsewhere on the board
GND: C1.2, C2.2, C3.2, J1.2, J2.9, J2.10, J2.19, J2.20, J2.29, J2.30, J2.39, J2.40, J2.43, J2.49, J2.50, J2.59, J2.60, J2.69, J2.70, J2.79, J2.80, Q4.1 (G), R2.1, U1.2 (GND); also elsewhere on the board
unnamed: R1.2, R2.2, U1.5 (FB)
unnamed: L1.1, U1.3 (SW)
PDM_CLK: J2.45; also elsewhere on the board
TCXO_CLK: J2.41; also elsewhere on the board

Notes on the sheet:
Q4: P-MOSFET reverse-polarity protection on the +5V input (drain to J1, source to +5V, gate to GND). Body diode conducts first; the channel then turns on (~0.05 V drop).
